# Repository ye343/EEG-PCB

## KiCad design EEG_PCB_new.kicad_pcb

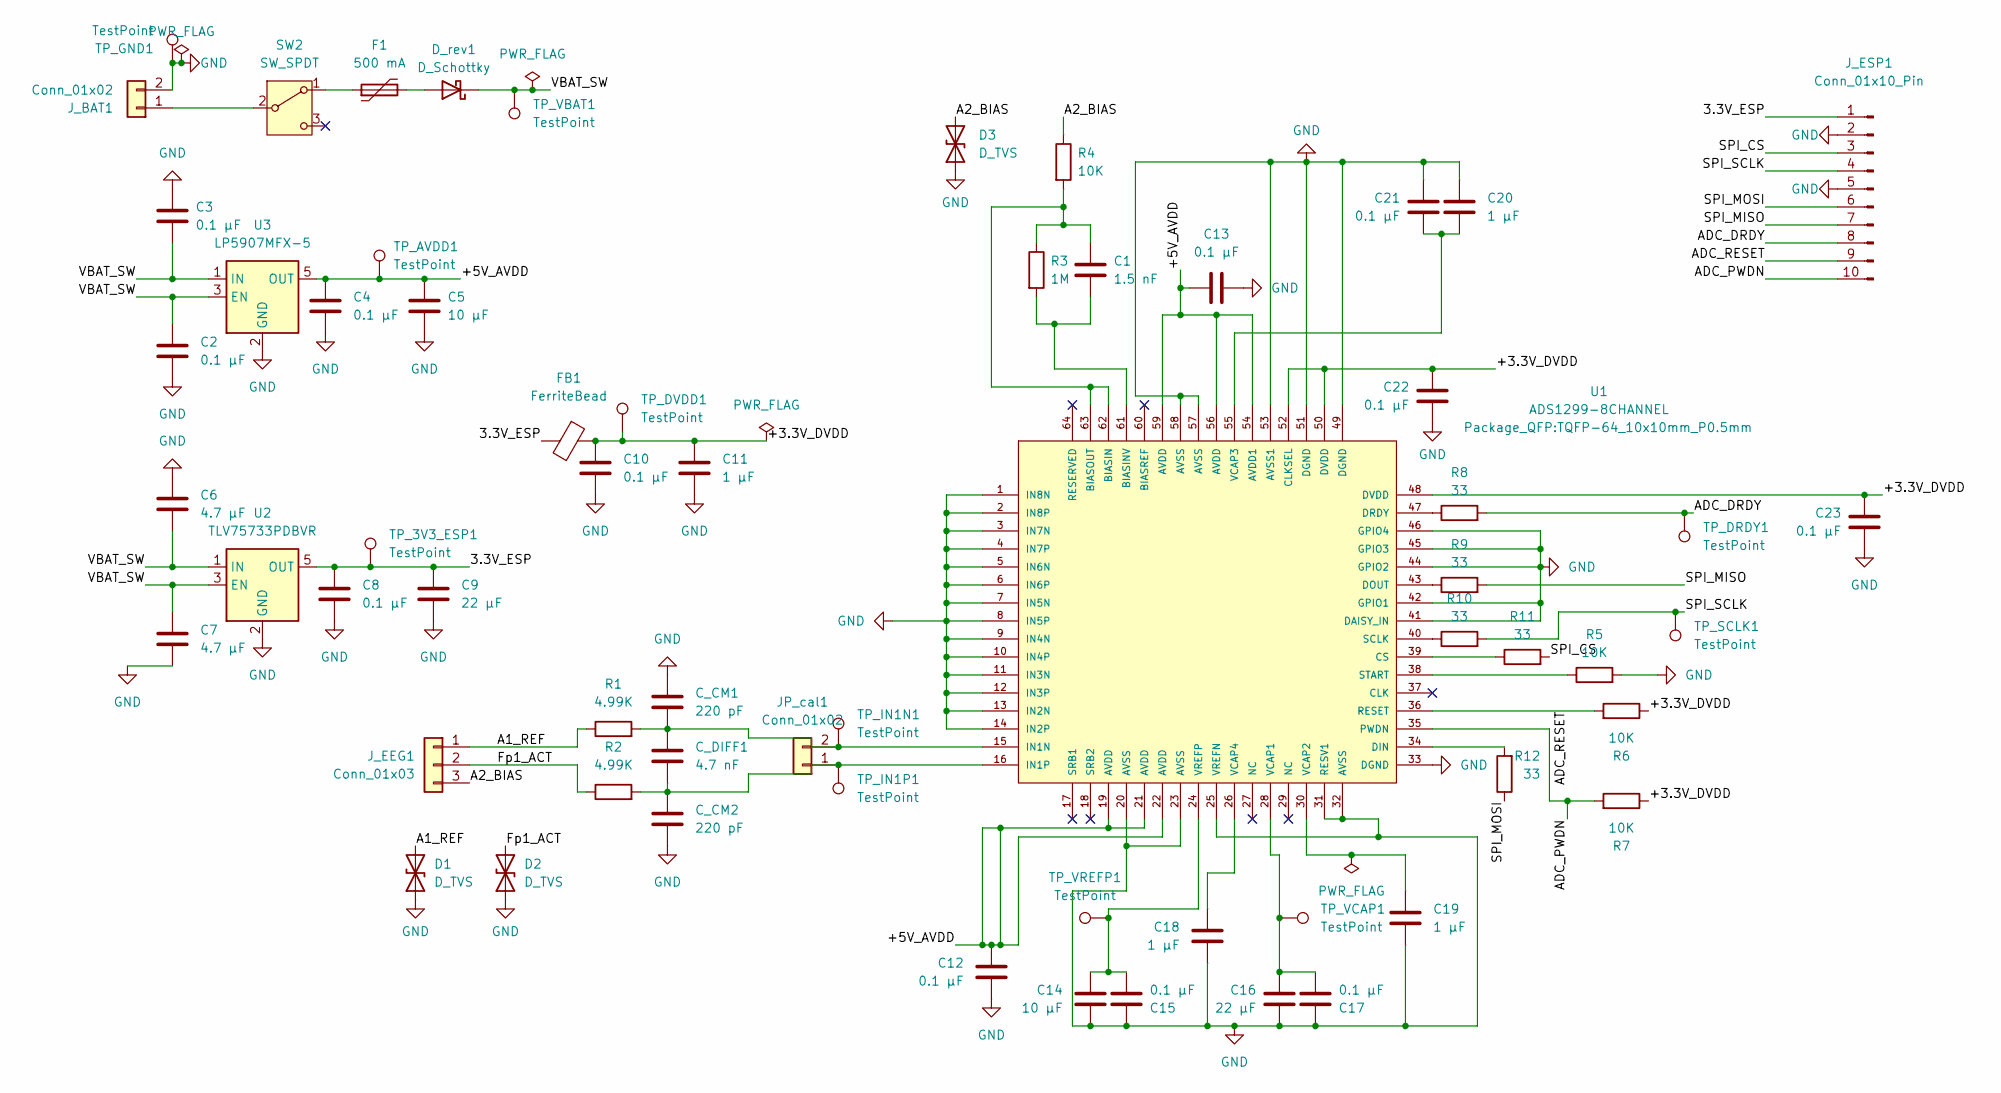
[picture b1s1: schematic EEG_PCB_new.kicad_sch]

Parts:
C1: 1.5 nF; C_0603_1608Metric
C2, C3, C4, C8, C10, C12, C13, C15, C17, C21, C22, C23: 0.1 µF; C_0603_1608Metric
C5, C14: 10 µF; C_0805_2012Metric
C6, C7: 4.7 µF; C_0805_2012Metric
C9, C16: 22 µF; C_0805_2012Metric
C11, C18, C19, C20: 1 µF; C_0603_1608Metric
C_CM1, C_CM2: 220 pF; C_0603_1608Metric
C_DIFF1: 4.7 nF; C_0603_1608Metric
D1, D2, D3: D_TVS; D_SOD-323
D_rev1: D_Schottky; D_SOD-123
F1: 500 mA; Fuse_1206_3216Metric
FB1: FerriteBead; L_0805_2012Metric
JP_cal1: Conn_01x02; PinHeader_1x02_P2.54mm_Vertical
J_BAT1: Conn_01x02; PinHeader_1x02_P2.54mm_Vertical
J_EEG1: Conn_01x03; PinHeader_1x03_P2.54mm_Vertical
J_ESP1: Conn_01x10_Pin; PinHeader_1x10_P2.54mm_Vertical
R1, R2: 4.99K; R_0603_1608Metric
R3: 1M; R_0603_1608Metric
R4, R5, R6, R7: 10K; R_0603_1608Metric
R8, R9, R10, R11, R12: 33; R_0603_1608Metric
SW2: SW_SPDT; SW_CK_JS202011CQN_DPDT_Straight
TP_3V3_ESP1: TestPoint; TestPoint_Pad_D1.5mm
TP_AVDD1: TestPoint; TestPoint_Pad_D1.5mm
TP_DRDY1: TestPoint; TestPoint_Pad_D1.5mm
TP_DVDD1: TestPoint; TestPoint_Pad_D1.5mm
TP_GND1: TestPoint; TestPoint_Pad_D1.5mm
TP_IN1N1, TP_IN1P1: TestPoint; TestPoint_Pad_D1.5mm
TP_SCLK1: TestPoint; TestPoint_Pad_D1.5mm
TP_VBAT1: TestPoint; TestPoint_Pad_D1.5mm
TP_VCAP1: TestPoint; TestPoint_Pad_D1.5mm
TP_VREFP1: TestPoint; TestPoint_Pad_D1.5mm
U1: ADS1299-8CHANNEL; TQFP-64_10x10mm_P0.5mm
U2: TLV75733PDBVR; SOT-23-5
U3: LP5907MFX-5; SOT-23-5

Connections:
/3.3V_ESP: C8.1, C9.1, FB1.2, J_ESP1.1, TP_3V3_ESP1.1, U2.5 (OUT)
/+3.3V_DVDD: C10.1, C11.1, C22.2, C23.2, FB1.1, R6.1, R7.1, TP_DVDD1.1, U1.48 (DVDD), U1.50 (DVDD), U1.52 (CLKSEL)
/+5V_AVDD: C4.1, C5.1, C12.1, C13.1, TP_AVDD1.1, U1.19 (AVDD), U1.21 (AVDD), U1.22 (AVDD), U1.54 (AVDD1), U1.56 (AVDD), U1.59 (AVDD), U3.5 (OUT)
/A1_REF: D1.2 (A2), J_EEG1.1, R1.1
/A2_BIAS: D3.2 (A2), J_EEG1.3, R4.1
/ADC_DRDY: J_ESP1.8, R8.2, TP_DRDY1.1
/ADC_PWDN: J_ESP1.10, R7.2, U1.35 (PWDN)
/ADC_RESET: J_ESP1.9, R6.2, U1.36 (RESET)
/Fp1_ACT: D2.2 (A2), J_EEG1.2, R2.1
/SPI_CS: J_ESP1.3, R11.2
/SPI_MISO: J_ESP1.7, R9.2
/SPI_MOSI: J_ESP1.6, R12.1
/SPI_SCLK: J_ESP1.4, R10.2, TP_SCLK1.1
/VBAT_SW: C2.1, C3.2, C6.2, C7.1, D_rev1.1 (K), TP_VBAT1.1, U2.1 (IN), U2.3 (EN), U3.1 (IN), U3.3 (EN)
GND: C2.2, C3.1, C4.2, C5.2, C6.1, C7.2, C8.2, C9.2, C10.2, C11.2, C12.2, C13.2, C14.1, C15.2, C16.1, C17.2, C18.2, C19.2, C20.1, C21.2, C22.1, C23.1, C_CM1.1, C_CM2.2, D1.1 (A1), D2.1 (A1), D3.1 (A1), J_BAT1.2, J_ESP1.2, J_ESP1.5, R5.2, TP_GND1.1, U1.1 (IN8N), U1.2 (IN8P), U1.3 (IN7N), U1.4 (IN7P), U1.5 (IN6N), U1.6 (IN6P), U1.7 (IN5N), U1.8 (IN5P), U1.9 (IN4N), U1.10 (IN4P), U1.11 (IN3N), U1.12 (IN3P), U1.13 (IN2N), U1.14 (IN2P), U1.20 (AVSS), U1.23 (AVSS), U1.25 (VREFN), U1.31 (RESV1), U1.32 (AVSS), U1.33 (DGND), U1.41 (DAISY_IN), U1.42 (GPIO1), U1.44 (GPIO2), U1.45 (GPIO3), U1.46 (GPIO4), U1.49 (DGND), U1.51 (DGND), U1.53 (AVSS1), U1.57 (AVSS), U1.58 (AVSS), U2.2 (GND), U3.2 (GND)
unnamed: D_rev1.2 (A), F1.2
unnamed: C_CM2.1, C_DIFF1.2, JP_cal1.1, R2.2, TP_IN1P1.1, U1.16 (IN1P)
unnamed: C_CM1.2, C_DIFF1.1, JP_cal1.2, R1.2, TP_IN1N1.1, U1.15 (IN1N)
unnamed: J_BAT1.1, SW2.2 (B)
unnamed: F1.1, SW2.1 (A)
unnamed: C1.1, R3.1, R4.2, U1.62 (BIASIN), U1.63 (BIASOUT)
unnamed: C1.2, R3.2, U1.61 (BIASINV)
unnamed: R11.1, U1.39 (CS)
unnamed: R12.2, U1.34 (DIN)
unnamed: R9.1, U1.43 (DOUT)
unnamed: R8.1, U1.47 (DRDY)
unnamed: R10.1, U1.40 (SCLK)
unnamed: R5.1, U1.38 (START)
unnamed: C16.2, C17.1, TP_VCAP1.1, U1.28 (VCAP1)
unnamed: C19.1, U1.30 (VCAP2)
unnamed: C20.2, C21.1, U1.55 (VCAP3)
unnamed: C18.1, U1.26 (VCAP4)
unnamed: C14.2, C15.1, TP_VREFP1.1, U1.24 (VREFP)

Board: 2 copper layers, 63 parts (0 on the bottom side), 33 nets, no tracks yet.
